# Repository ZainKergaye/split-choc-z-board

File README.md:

# Choc split-key z-board

The choc split key zboard is another ergonomic split-keyboard designed for comfort and efficiency. Using wired USB-C connectors to communicate between halves, it is a plain simple keyboard.

## Table of Contents

1. [Introduction](#introduction)
2. [Features](#features)
3. [Getting Started](#getting-started)
4. [Hardware](#hardware)
5. [Initial Board Testing](#initial-board-testing)
6. [Assembly](#assembly)
7. [Firmware Installation](#firmware-installation)
8. [Troubleshooting](#troubleshooting)

## Features

- Ergonomic split design for improved comfort
- Custom PCB with SMD and THC components
- Open-source firmware using [QMK](https://docs.qmk.fm).
- 3D printed [case](https://www.printables.com/@ZainKergaye_241410)

## Getting Started

To make your own keyboard order all the parts in the [hardware](#hardware) section. Solder
everything according to the silkscreen, be prepared to solder SMD and THC components. 3D
print the case. Build and flash the firmware. Then you are done!

## Hardware

### PCB

Order the PCB from any manufacurer you want, the exported gerbers are below.

[Left half gerbers](./split-choc-z-board/gerbers/left-half-gerbers.zip)

### Components

[Choc v1 switches](https://www.amazon.com/dp/B0BLC9BKW8)

[Keycaps](https://www.amazon.com/dp/B0D2DCDBSW)

[QSPI Flash](https://www.digikey.com/en/products/detail/winbond-electronics/W25Q128JVSIQ-TR/5803944)

[RP2040](https://www.digikey.com/en/products/detail/raspberry-pi/SC0914-13/14306010?s=N4IgTCBcDaIE4AcwAYAsyQF0C%2BQ)

[Button](https://www.digikey.com/en/products/detail/e-switch/TL3315NF250Q/1870396)

[Resistor 10k](https://www.digikey.com/en/products/detail/bourns-inc/CR0603-FX-1002ELF/3593188)

[Resistor 27.4k](https://www.digikey.com/en/products/detail/bourns-inc/CR0603-FX-27R4ELF/3783905)

[Resistor 4.99k](https://www.digikey.com/en/products/detail/bourns-inc/CR0603-FX-4991ELF/2345092)

[Resistor 1k](https://www.digikey.com/en/products/detail/bourns-inc/CR0603-JW-102ELF/3741004)

[Capacitor 15pf](https://www.digikey.com/en/products/detail/murata-electronics/GCM1555C1H150JA16D/4903554)

[Capacitor 10uf](https://www.digikey.com/en/products/detail/samsung-electro-mechanics/CL05A106MQ5NUNC/3887109)

[Capacitor 1uf](https://www.digikey.com/en/products/detail/taiyo-yuden/JMK105BJ105KV-F/930583)

[Capacitor 0.1uf](https://www.digikey.com/en/products/detail/samsung-electro-mechanics/CL05B104KP5NNNC/3886660)

[USB-C connector](https://www.digikey.com/en/products/detail/gct/USB4105-GF-A/11198441)

[Diodes](https://www.digikey.com/en/products/detail/mcc-micro-commercial-components/1N4148W-TP/717196)

[Electrostatic protection](https://www.digikey.com/en/products/detail/umw/usblc6-2sc6/16705896)

One USB-C data cable to communicate between halves and one more to communicate to the computer.

### Additional tools

- Hot air soldering station / Reflow oven
- Soldering iron
- Solder wire
- Solder paste (For SMD)
- Rosin

## Initial Board Testing

While assembling the board, it's very important to make sure the RP2040 works.
Solder the main chip along with the top USB-C connector, Power regulation, QSPI flash,
and all the other decoupling capacitors and resistors. Don't solder the lower USB-C or
it's ESD protection or any other keyswitches. GPIO 24 is exposed through the 2.7mm dupont holes.
Simply connect an led and 1k ohm resistor to it and upload blink.py. This will give you a basic
program that tells you if the whole chip works or not.

## Assembly

> [!NOTE]
> Currently a work in progress, more pictures will be coming.

Assembly will require you to have kicad board editor open while you populate the board
in order to know which component goes where. Definately not recommended as a first beginner project.

## Firmware Installation

See the [build environment setup](https://docs.qmk.fm/#/getting_started_build_tools) and the [make instructions](https://docs.qmk.fm/#/getting_started_make_guide) for more information.

After setting up your build environment, simply use this command to flash

```bash

make e88:default:flash

```

## Troubleshooting

If you have encountered any problems or issues, feel free to create an issue [here](https://github.com/ZainKergaye/split-choc-z-board/issues)!

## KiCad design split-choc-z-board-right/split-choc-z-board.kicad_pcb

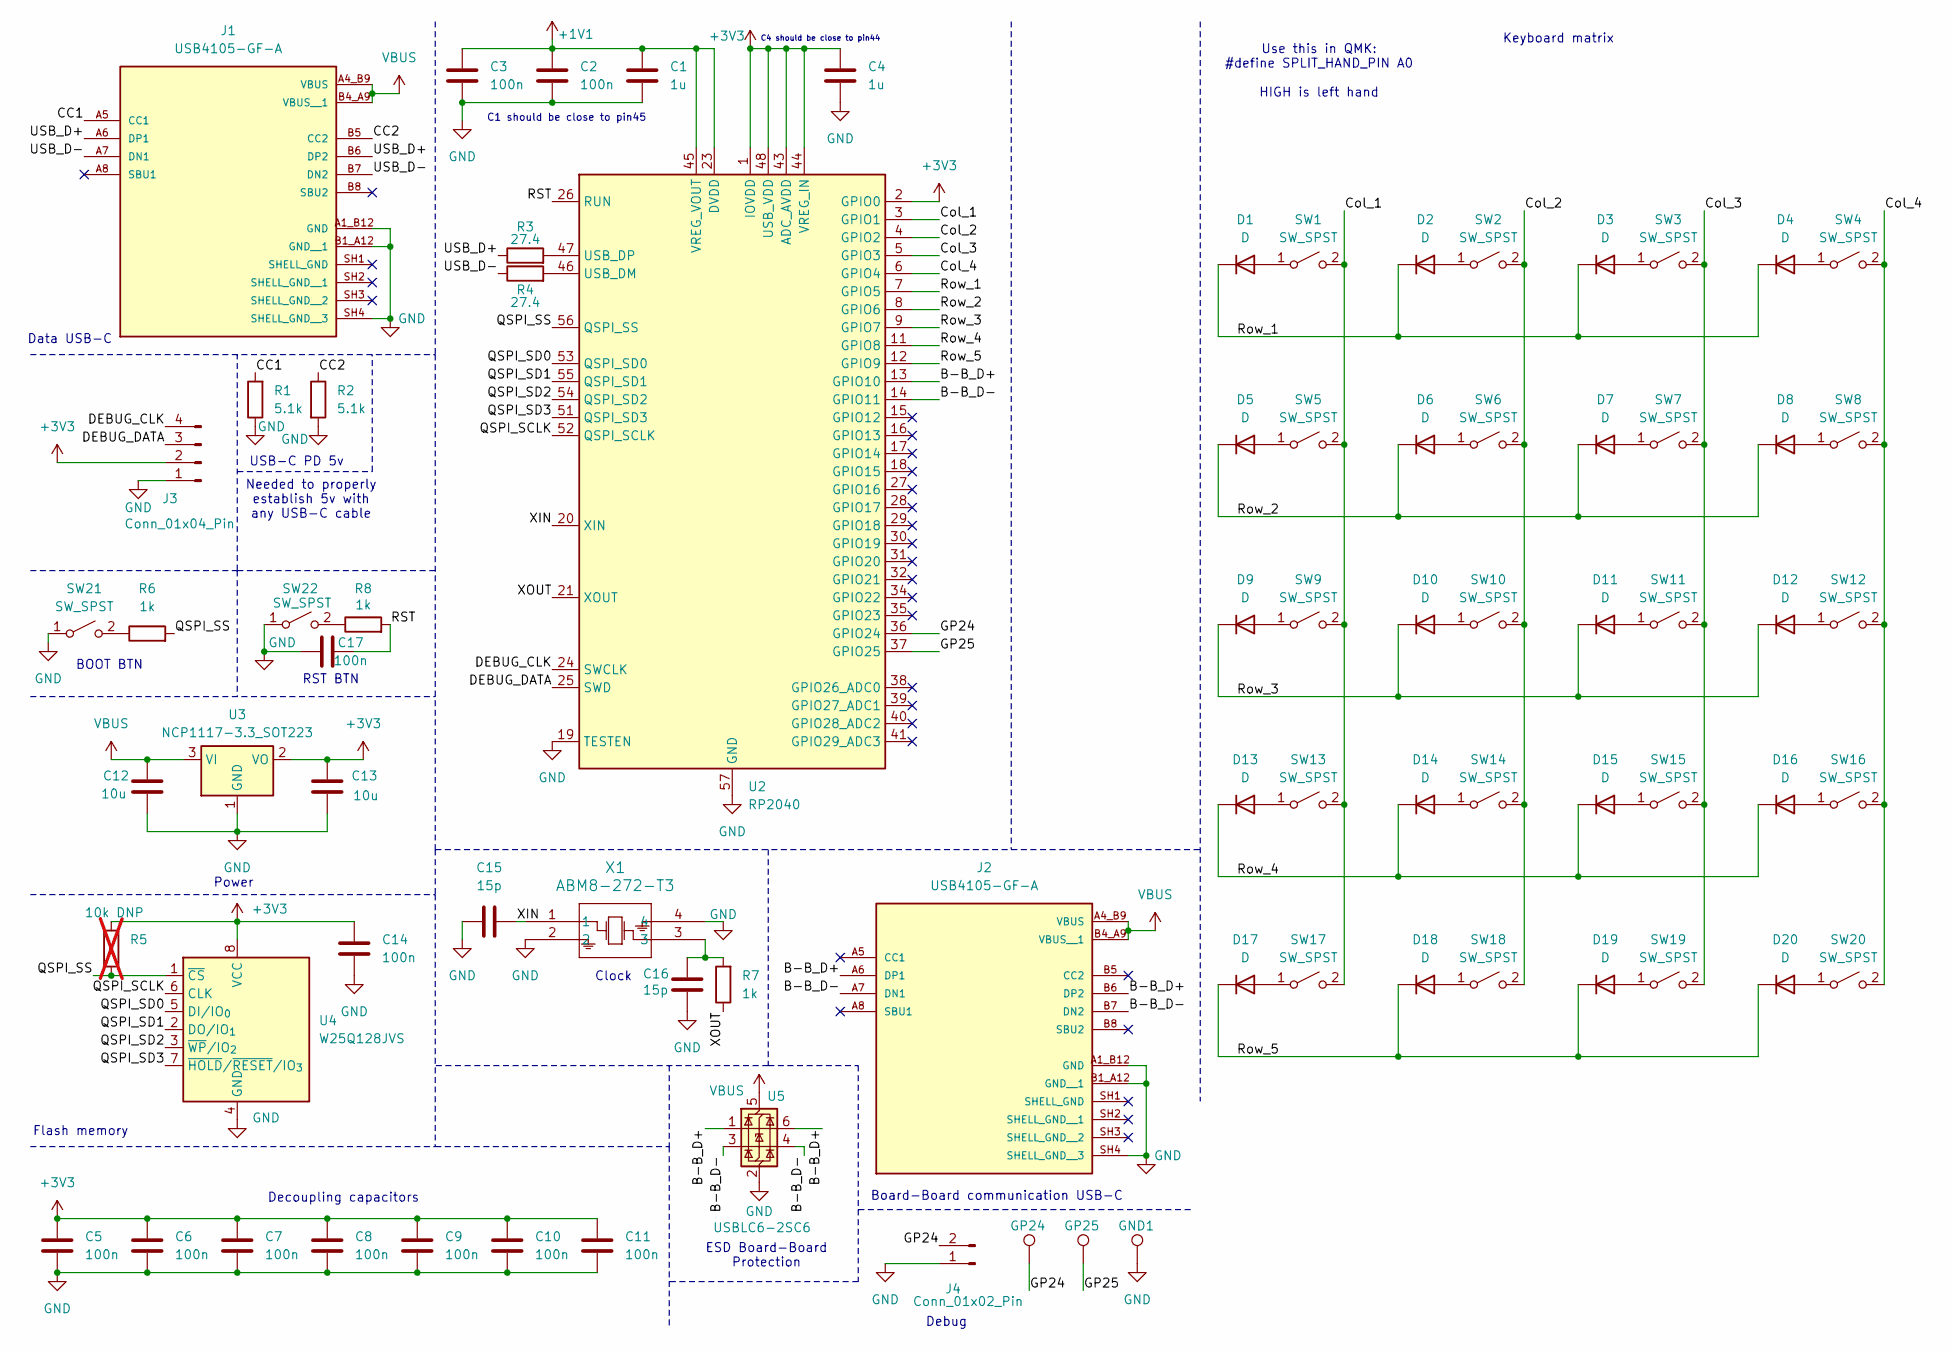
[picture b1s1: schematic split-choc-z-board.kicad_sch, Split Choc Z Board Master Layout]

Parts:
C1, C4: 1u; C_0402_1005Metric
C2, C3, C5, C6, C7, C8, C9, C10, C11, C14, C17: 100n; C_0402_1005Metric
C12, C13: 10u; C_0402_1005Metric
C15, C16: 15p; C_0402_1005Metric
D1, D2, D3, D4, D5, D6, D7, D8, D9, D10, D11, D12, D13, D14, D15, D16, D17, D18, D19, D20: D; SOD123_MCC
GND1: TestPoint; TestPoint_Pad_D2.0mm
GP24, GP25: TestPoint; TestPoint_Pad_D2.0mm
J1, J2: USB4105-GF-A; GCT_USB4105-GF-A; PARTREV B4
J3: Conn_01x04_Pin; PinHeader_1x04_P2.54mm_Vertical
J4: Conn_01x02_Pin; PinHeader_1x02_P2.54mm_Vertical
R1, R2: 5.1k; R_0603_1608Metric
R3, R4: 27.4; R_0603_1608Metric
R5: 10k DNP; R_0603_1608Metric; not fitted
R6, R7, R8: 1k; R_0603_1608Metric
SW1, SW2, SW3, SW4, SW5, SW6, SW7, SW8, SW9, SW10, SW11, SW12, SW13, SW14, SW15, SW16, SW17, SW18, SW19, SW20: SW_SPST; Choc_V1_1.00u
SW21, SW22: SW_SPST; SW_TL3315NF250Q
U2: RP2040; QFN-56-1EP_7x7mm_P0.4mm_EP3.2x3.2mm
U3: NCP1117-3.3_SOT223; SOT-223-3_TabPin2
U4: W25Q128JVS; SOIC-8_5.3x5.3mm_P1.27mm
U5: USBLC6-2SC6; SOT-23-6
X1: ABM8-272-T3; ABM8-272-T3_ABR

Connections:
+1V1: C1.1, C2.1, C3.1, U2.23 (DVDD), U2.45 (VREG_VOUT), U2.50 (DVDD)
+3V3: C4.1, C5.1, C6.1, C7.1, C8.1, C9.1, C10.1, C11.1, C13.1, C14.1, J3.2, R5.1, U2.1 (IOVDD), U2.2 (GPIO0), U2.10 (IOVDD), U2.22 (IOVDD), U2.33 (IOVDD), U2.42 (IOVDD), U2.43 (ADC_AVDD), U2.44 (VREG_IN), U2.48 (USB_VDD), U2.49 (IOVDD), U3.2 (VO), U4.8 (VCC)
/B-B_D+: J2.A6 (DP1), J2.B6 (DP2), U2.13 (GPIO10), U5.1 (I/O1), U5.6 (I/O1)
/B-B_D-: J2.A7 (DN1), J2.B7 (DN2), U2.14 (GPIO11), U5.3 (I/O2), U5.4 (I/O2)
/CC1: J1.A5 (CC1), R1.2
/CC2: J1.B5 (CC2), R2.1
/Col_1: SW1.2 (B), SW5.2 (B), SW9.2 (B), SW13.2 (B), SW17.2 (B), U2.3 (GPIO1)
/Col_2: SW2.2 (B), SW6.2 (B), SW10.2 (B), SW14.2 (B), SW18.2 (B), U2.4 (GPIO2)
/Col_3: SW3.2 (B), SW7.2 (B), SW11.2 (B), SW15.2 (B), SW19.2 (B), U2.5 (GPIO3)
/Col_4: SW4.2 (B), SW8.2 (B), SW12.2 (B), SW16.2 (B), SW20.2 (B), U2.6 (GPIO4)
/DEBUG_CLK: J3.4, U2.24 (SWCLK)
/DEBUG_DATA: J3.3, U2.25 (SWD)
/GP24: GP24.1, J4.2, U2.36 (GPIO24)
/GP25: GP25.1, U2.37 (GPIO25)
/QSPI_SCLK: U2.52 (QSPI_SCLK), U4.6 (CLK)
/QSPI_SD0: U2.53 (QSPI_SD0), U4.5 (DI/IO_{0})
/QSPI_SD1: U2.55 (QSPI_SD1), U4.2 (DO/IO_{1})
/QSPI_SD2: U2.54 (QSPI_SD2), U4.3 (~WP/IO_{2})
/QSPI_SD3: U2.51 (QSPI_SD3), U4.7 (~HOLD/~RESET/IO_{3})
/QSPI_SS: R5.2, R6.2, U2.56 (QSPI_SS), U4.1 (~CS)
/RST: C17.2, R8.2, U2.26 (RUN)
/Row_1: D1.1 (K), D2.1 (K), D3.1 (K), D4.1 (K), U2.7 (GPIO5)
/Row_2: D5.1 (K), D6.1 (K), D7.1 (K), D8.1 (K), U2.8 (GPIO6)
/Row_3: D9.1 (K), D10.1 (K), D11.1 (K), D12.1 (K), U2.9 (GPIO7)
/Row_4: D13.1 (K), D14.1 (K), D15.1 (K), D16.1 (K), U2.11 (GPIO8)
/Row_5: D17.1 (K), D18.1 (K), D19.1 (K), D20.1 (K), U2.12 (GPIO9)
/USB_D+: J1.A6 (DP1), J1.B6 (DP2), R3.1
/USB_D-: J1.A7 (DN1), J1.B7 (DN2), R4.1
/XIN: C15.2, U2.20 (XIN), X1.1
/XOUT: R7.1, U2.21 (XOUT)
GND: C1.2, C2.2, C3.2, C4.2, C5.2, C6.2, C7.2, C8.2, C9.2, C10.2, C11.2, C12.2, C13.2, C14.2, C15.1, C16.2, C17.1, GND1.1, J1.A1_B12 (GND), J1.B1_A12 (GND__1), J1.SH4 (SHELL_GND__3), J2.A1_B12 (GND), J2.B1_A12 (GND__1), J2.SH4 (SHELL_GND__3), J3.1, J4.1, R1.1, R2.2, SW21.1 (A), SW22.1 (A), U2.19 (TESTEN), U2.57 (GND), U3.1 (GND), U4.4 (GND), U5.2 (GND), X1.2, X1.4
unnamed: C16.1, R7.2, X1.3
unnamed: D1.2 (A), SW1.1 (A)
unnamed: D2.2 (A), SW2.1 (A)
unnamed: D3.2 (A), SW3.1 (A)
unnamed: D4.2 (A), SW4.1 (A)
unnamed: D5.2 (A), SW5.1 (A)
unnamed: D6.2 (A), SW6.1 (A)
unnamed: D7.2 (A), SW7.1 (A)
unnamed: D8.2 (A), SW8.1 (A)
unnamed: D9.2 (A), SW9.1 (A)
unnamed: D10.2 (A), SW10.1 (A)
unnamed: D11.2 (A), SW11.1 (A)
unnamed: D12.2 (A), SW12.1 (A)
unnamed: D13.2 (A), SW13.1 (A)
unnamed: D14.2 (A), SW14.1 (A)
unnamed: D15.2 (A), SW15.1 (A)
unnamed: D16.2 (A), SW16.1 (A)
unnamed: D17.2 (A), SW17.1 (A)
unnamed: D18.2 (A), SW18.1 (A)
unnamed: D19.2 (A), SW19.1 (A)
unnamed: D20.2 (A), SW20.1 (A)
unnamed: R6.1, SW21.2 (B)
unnamed: R8.1, SW22.2 (B)
unnamed: R4.2, U2.46 (USB_DM)
unnamed: R3.2, U2.47 (USB_DP)
VBUS: C12.1, J1.A4_B9 (VBUS), J1.B4_A9 (VBUS__1), J2.A4_B9 (VBUS), J2.B4_A9 (VBUS__1), U3.3 (VI), U5.5 (VBUS)

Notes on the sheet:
BOOT BTN
Use this in QMK: #define SPLIT_HAND_PIN A0 HIGH is left hand
Clock
RST BTN
Flash memory
C1 should be close to pin45
Debug
Data USB-C
Board-Board communication USB-C
Keyboard matrix
C4 should be close to pin44
USB-C PD 5v
Decoupling capacitors
Power
ESD Board-Board Protection
Needed to properly establish 5v with any USB-C cable

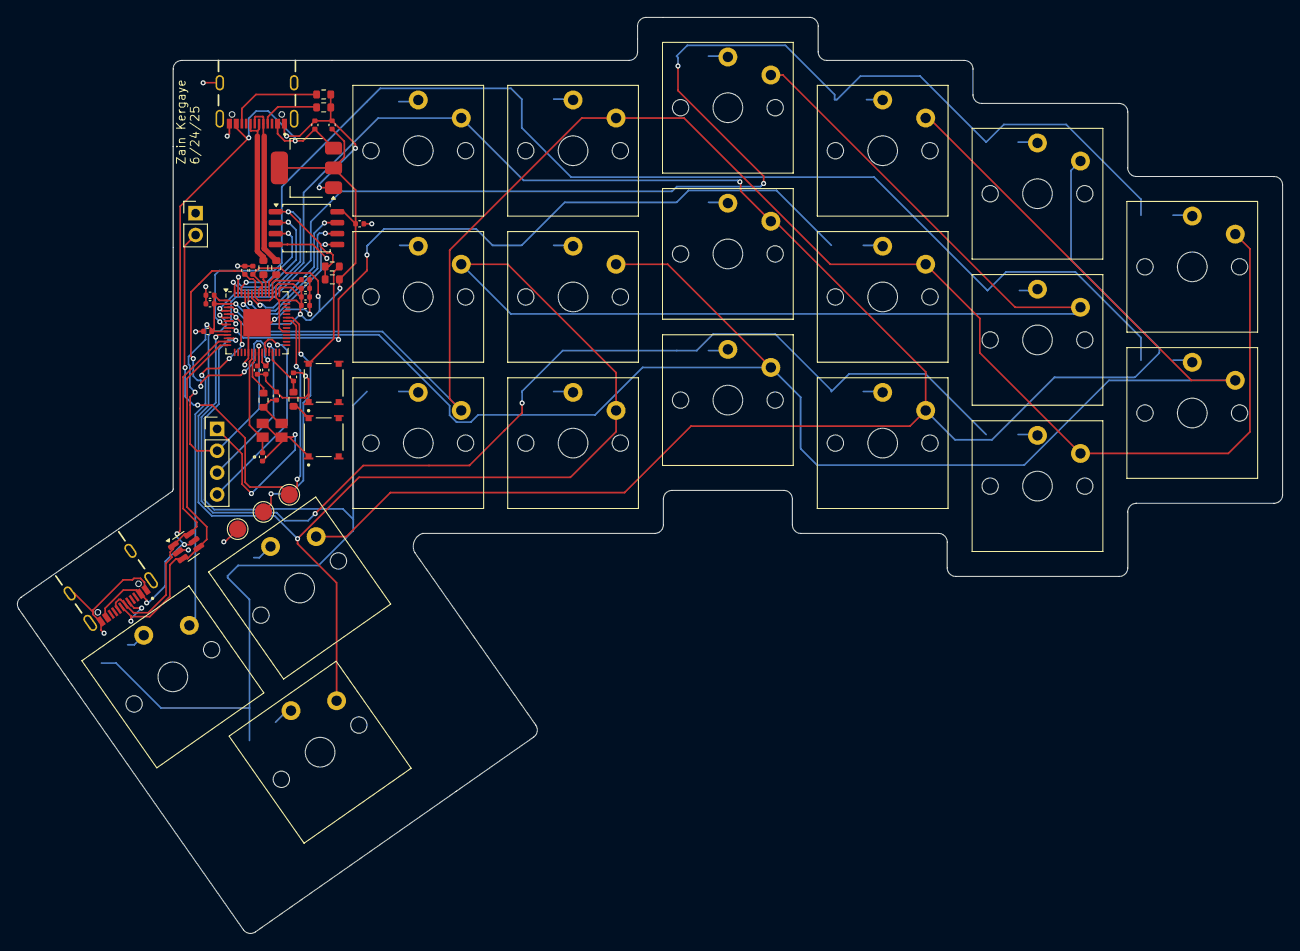
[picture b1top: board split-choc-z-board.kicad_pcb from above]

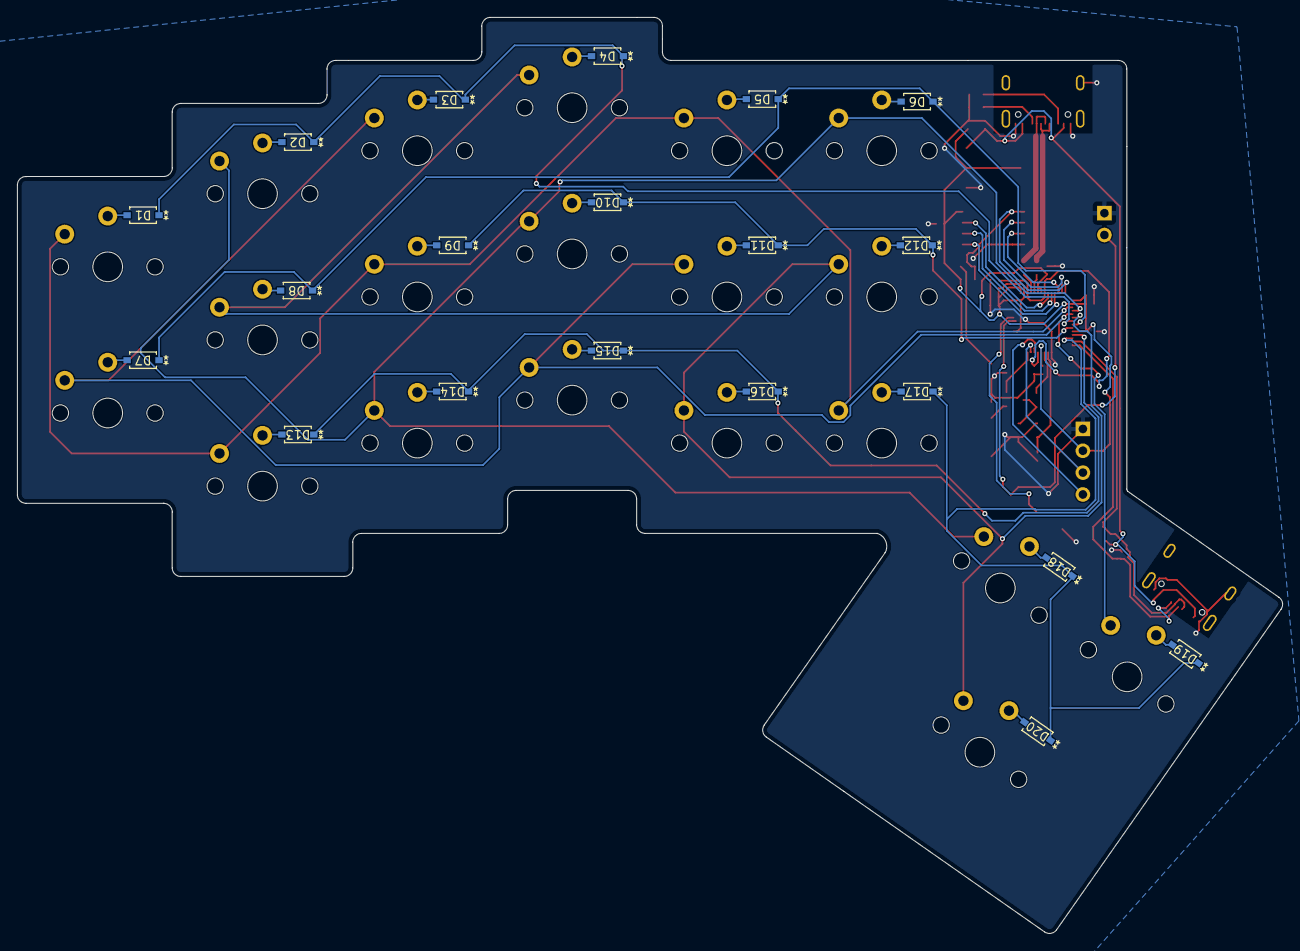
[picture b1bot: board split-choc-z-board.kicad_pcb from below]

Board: 2 copper layers, 147.1 x 106.5 mm, 79 parts (20 on the bottom side), 57 nets.

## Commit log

2025-03-25 Added more clarification
2025-05-07 Finished basic layout and just started making split board from main sch
2025-05-08 Refactored schematic and added footprint library
2025-05-08 Added more footprints to symbols and started placement
2025-05-09 Changed TTRS to USB C
2025-05-11 Update: Defined components in README and added ESD protection. Also changed USBC connector
2025-05-11 Update: Added more footprints 🚀
2025-05-11 Adding more to pcb
2025-05-12 Finalized placement of components 🎉 and defined edge
2025-05-12 Fixed edgecut DRC. Ready for routing!
2025-05-12 Added right half! Flipped PCB, tx and rx on USBC, and handness pin
2025-05-12 Finished routing right side! 🤖
2025-05-12 Routed left side! 😃
2025-05-12 Added text on silkscreen
2025-05-12 Update: Exported gerbers!
2025-05-14 Not sure what changed here
2025-05-18 Updated README! 🙋
2025-05-18 Added firmware as submodule
2025-05-18 Adding more docs 📘
2025-05-20 Adding more docs
2025-06-14 Removed right side, need to redo MCU 😢
2025-06-15 Added kb library for 128x32 oled display and deleted MCU 🥳
2025-06-16 Added RP2040! 😅 Hopefully no errors to come
2025-06-17 Added debug pads
2025-06-17 Updated README 📕
2025-06-18 Placed all components properly! 😄
2025-06-18 Finished board outline 🖥️
2025-06-18 Moved switch layout around and changed constraints for JLCPCB ⚡
2025-06-18 Copied project for right side
2025-06-18 Finalized component placement! 💡
2025-06-19 Almost done routing left side
2025-06-20 Almost finished left half routing
2025-06-20 Routed left side
2025-06-21 Finished routing USB and added easier to use debug connectors
2025-06-21 Updated right side schematic to match left
2025-06-22 Copied left hand component placement changes to right hand
2025-06-23 Routing right side!
2025-06-23 Finished routing right! 👏🏻
2025-06-24 Finished cleaning up left side! 🥳
2025-06-24 Finished up right half! 🎉
2025-06-24 Added gerbers
2025-06-25 Added name and date to board
2025-06-25 Added name and date to board 2
2025-06-26 Added basic blink script for testing
2025-06-26 Updating submodule 📕
2025-06-29 Added more to README! 🥸
